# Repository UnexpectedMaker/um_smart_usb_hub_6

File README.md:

# Smart 6 Port USB Hub

**Automated testing. Automated device control.**

**Designed and made by [Unexpected Maker](https://unexpectedmaker.com) ·
[Get one from the store →](https://unexpectedmaker.com/shop/smarthub)**

Built for developers, test benches and USB devices that need to run unattended.
Smart USB Hub brings repeatable testing and everyday device routines to your
workbench, without the constant plugging, unplugging and reaching for cables.

## What it does

**Power cycling, scripted.** Use the REST API to switch a device's power, read
its voltage, current and power consumption, and check port status from your
test scripts. Repeat a startup test or compare readings across operating states
while the other devices stay powered.

**Every port, scheduled.** Set a different schedule for each port: selected
weekdays, a fixed run time, a chosen stop time or repeating intervals. Rules run
on the hub, so your browser doesn't need to stay open.

**Step in any time.** Open the web interface over Wi-Fi to switch an individual
port or investigate a device. Live readings show what it's drawing; connection
and fault status help you see why it isn't behaving as expected.

## Specifications

| | |
|---|---|
| Downstream | 6 × USB-C · USB 2.0 High Speed (480 Mbps) on every port |
| Upstream | 1 × USB-C · USB 2.0 High Speed (480 Mbps) |
| Hub chip | WCH CH339W · Multi-TT: every port has its own transaction translator, so full-speed and low-speed devices don't share bandwidth |
| Controller | ESP32-S3-WROOM-1 · 16 MB flash · 8 MB PSRAM |
| Port power | 5V USB-C input · 3A+ supply |
| 3V3 power | 2 × 3.3V LDOs · headroom for the ESP32-S3, hub chip, peripherals and LEDs |
| Protection | Per-port current limiting and over-current fault detection |
| Monitoring | Per-port voltage, current and power |
| Indicators | Per-port RGB status · power, device presence and faults |
| Environment | Onboard temperature and humidity sensor |
| Buttons | IO48 user button · IO0 / Boot · Reset |
| Case size | 90 mm × 64 mm × 19 mm |

## Web interface

## It's open source

Smart USB Hub is fully open source, so you can see exactly how it works, tweak
it to suit your bench, or build your own. Everything is in this repository:

| Folder | Contents |
|---|---|
| [`firmware/`](firmware/) | The PlatformIO project — building, flashing, first-time Wi-Fi setup and how to use the hub |
| [`hardware/`](hardware/) | KiCad 10 design files: schematic, PCB, footprints, 3D models and interactive BOM |
| [`docs/`](docs/) | Documentation: the [JSON / REST API reference](docs/rest_api.md), [port profiler](docs/profiler.md), [graph history](docs/graph_history.md) and [planned future updates](docs/future_updates.md) |
| [`step/`](step/) | STEP models of the board and the case, the light pipe insert, and the parts list for printing your own case |

Each folder has its own README with the details.

## Optional case

Add the case from the [store](https://unexpectedmaker.com/shop/smarthub) and
your hub goes from bare board to finished desk tool:

- **Matt black ABS** — a 3D printed enclosure that looks right at home on any
  bench
- **Laser cut light pipes** — every port's RGB status still shines through
- **Heat inserts + screws** — proper threads, so it goes together solid
- **Rubber feet** — it stays put when you plug and unplug

Or print your own from the files in [`step/`](step/) — its README covers the
light pipe insert and the screws, inserts and feet you'll need.

## Getting started

If you have a hub, start with **First-time setup** in the
[firmware README](firmware/README.md#first-time-setup). It gets the hub onto
your Wi-Fi so you can use the web interface.

## Licence

Copyright (c) 2026 [Unexpected Maker](https://unexpectedmaker.com).

| Part | Licence |
|---|---|
| Hardware (`hardware/`) and 3D files (`step/`) | [CERN-OHL-S v2](hardware/LICENSE) — strongly reciprocal: if you distribute the design, a modified version, or hardware made from it, you must publish the complete design source under the same licence |
| Firmware (`firmware/`) | [GPL-3.0-or-later](firmware/LICENSE) — use it, change it, put it in your own products; if you distribute it, you must publish the complete firmware source under the same licence. Bundled third-party code keeps its own licence (see the [firmware README](firmware/README.md#third-party-code)) |

Source location: <https://github.com/UnexpectedMaker/um_smart_usb_hub_6>

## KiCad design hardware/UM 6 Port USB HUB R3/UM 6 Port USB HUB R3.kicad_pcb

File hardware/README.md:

# Hardware

KiCad 10 project for the Unexpected Maker 6 Port Smart USB Hub (R3).

Open `UM 6 Port USB HUB R3/UM 6 Port USB HUB R3.kicad_pro` in KiCad 10 or later.

## Self-contained project

Everything that is not part of a standard KiCad installation is included in the project folder. No external or personal libraries are needed, and there are no absolute paths in any project file.

- **Footprints** – every non-stock footprint used on the board lives in the project library `UM_Hub.pretty`. It is registered through the project `fp-lib-table` using `${KIPRJMOD}`, so KiCad picks it up automatically when the project is opened.
- **3D models** – every non-stock model is in `3d models/` and is referenced relative to the project (`${KIPRJMOD}/3d models/...`). The 0805 resistor model is embedded in its footprint.
- **Stock parts** – the remaining footprints and models come from the default libraries installed with KiCad (`Capacitor_SMD`, `Package_DFN_QFN`, `Package_TO_SOT_SMD`, `RF_Module`, `MountingHole` and the standard `KICAD*_3DMODEL_DIR` models).
- **Symbols** – the schematic carries its own copy of every symbol it uses, so it opens and edits without any external symbol libraries.

## Contents of `UM 6 Port USB HUB R3/`

| Item | What it is |
|---|---|
| `UM 6 Port USB HUB R3.kicad_pro` | KiCad project file |
| `UM 6 Port USB HUB R3.kicad_sch` | Schematic |
| `UM 6 Port USB HUB R3.kicad_pcb` | PCB layout |
| `UM_Hub.pretty/` | Project footprint library (17 footprints) |
| `fp-lib-table` | Registers `UM_Hub` for this project |
| `3d models/` | STEP models for the non-stock parts |
| `bom/ibom.html` | Interactive HTML BOM |

## Manufacturing

If you are getting this board manufactured, the PCB stackup must match the following so that the USB differential pairs are impedance matched.

PCB Stackup: JLC04161H-3313 (Finished thickness 1.56mm ±10%)

90R Diff Pair Impedance:
- Trace 0.1545mm
- Gap 0.232mm
- Co-Planar Clearance 0.194mm

## Licence

Copyright (c) 2026 [Unexpected Maker](https://unexpectedmaker.com).

The hardware design files are licensed under the CERN Open Hardware Licence
Version 2 — Strongly Reciprocal (CERN-OHL-S v2). See [LICENSE](LICENSE).

If you distribute this design, a modified version of it, or hardware made from
it, you must make the complete design source available under the same licence.

Source location: <https://github.com/UnexpectedMaker/um_smart_usb_hub_6>

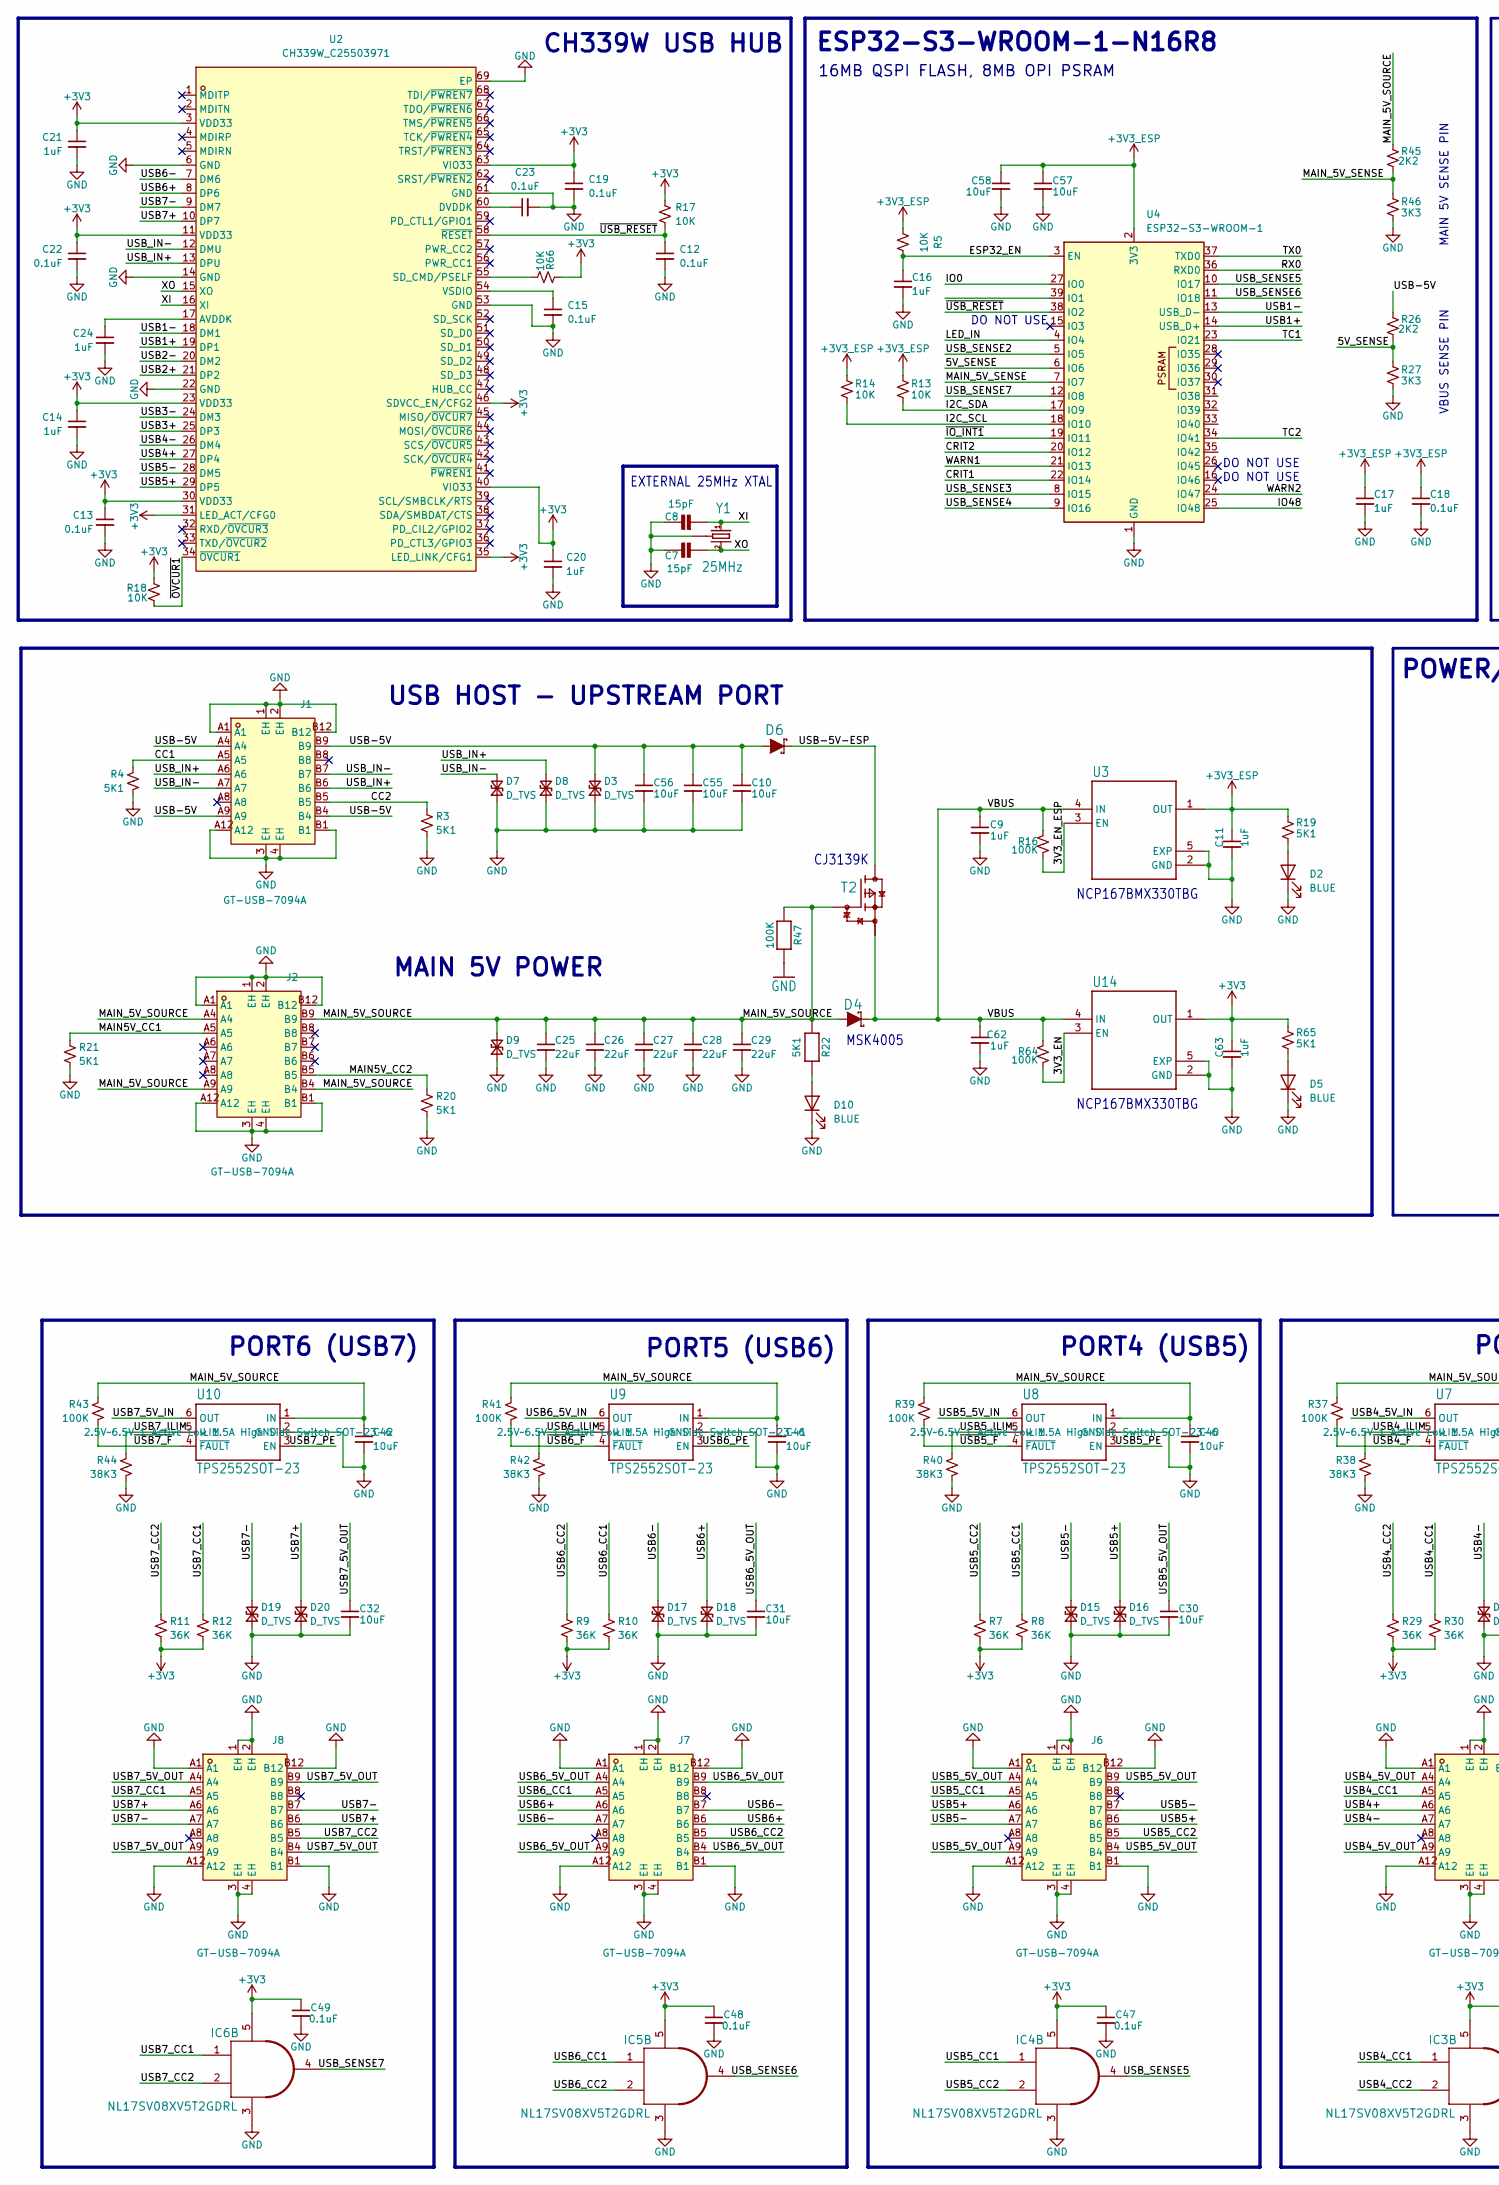
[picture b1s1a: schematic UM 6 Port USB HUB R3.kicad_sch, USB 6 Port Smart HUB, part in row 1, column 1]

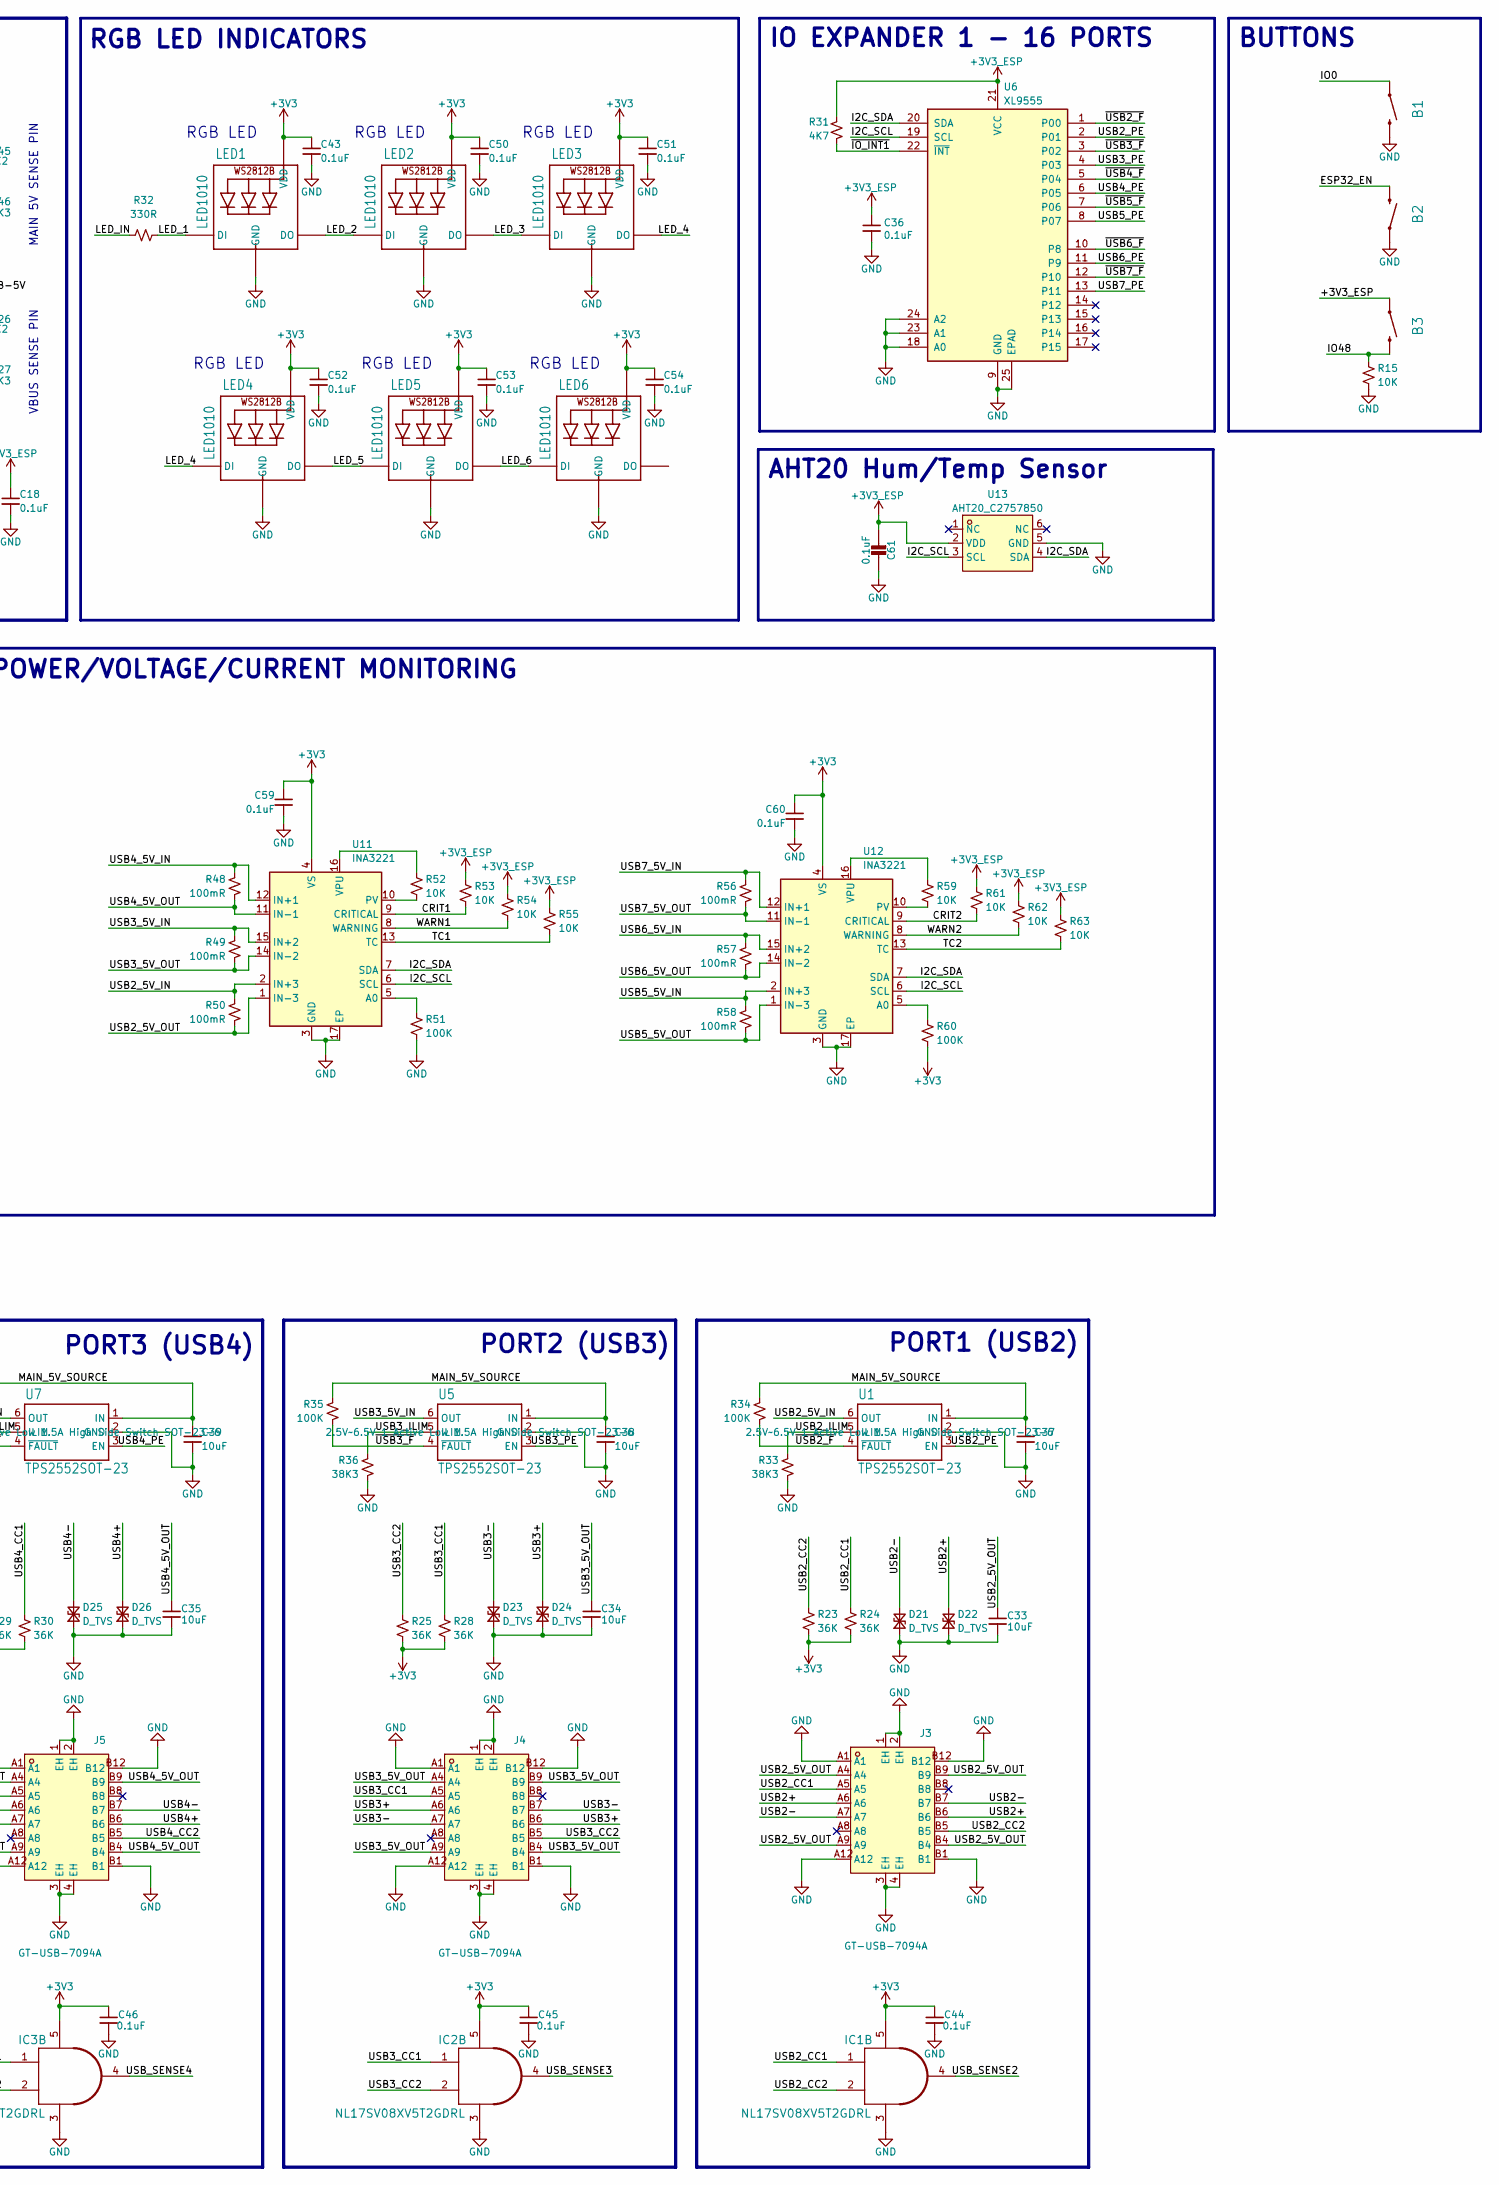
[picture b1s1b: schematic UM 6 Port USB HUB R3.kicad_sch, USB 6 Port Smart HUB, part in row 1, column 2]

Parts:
B1, B2, B3: MOMENTARY-SWITCH-SPST-PTH-RIGHT-ANGLE-KIT; SMT_SWITCH_TS-1091C-A6B3-D2; MPN TS-1091C-A7B3-D2
C7, C8: 15pF; C_0402_NEW; MPN CC0402FRNPO9BN150
C9, C11, C14, C16, C17, C20, C21, C24, C62, C63: 1uF; C_0402_NEW; MPN CL05A105KA5NQNC
C10, C30, C31, C32, C33, C34, C35, C37, C38, C39, C40, C41, C42, C55, C56, C57, C58: 10uF; C_0603_NEW; MPN CGA0603X5R106K250JT
C12, C13, C15, C18, C19, C22, C23, C36, C43, C44, C45, C46, C47, C48, C49, C50, C51, C52, C53, C54, C59, C60, C61: 0.1uF; C_0402_NEW; MPN 0402B104K500CT
C25, C26, C27, C28, C29: 22uF; C_1210_3225Metric; MPN CC1210KKX5R8BB226
D2, D5, D10: BLUE; LED_0402_NEW; MPN TJ-S1005SW4TGLC6B-A5
D3, D7, D8, D9, D15, D16, D17, D18, D19, D20, D21, D22, D23, D24, D25, D26: D_TVS; TVS X1-DFN1006-2-BEST; MPN ESD05V88D-LC
D4, D6: DIODE-SCHOTTKYWIDE; SOD-523-MSK4010; MPN MSK4010
IC1, IC2, IC3, IC4, IC5, IC6: NL17SV08XV5T2GDRL; SOT553; MPN NL17SV08XV5T2GDRL
J1, J2, J3, J4, J5, J6, J7, J8: GT-USB-7094A; CONN-SMD_GT-USB-7094A; MPN GT-USB-7094A; LCSC Part C22383838
LED1, LED2, LED3, LED4, LED5, LED6: LED1010; MPN XL-1010RGBC-2812B
R3, R4, R19, R20, R21, R22, R65: 5K1; R_0402_NEW; MPN 0402WGF5101TCE
R5, R13, R14, R15, R17, R18, R52, R53, R54, R55, R59, R61, R62, R63, R66: 10K; R_0402_NEW; MPN 0402WGF1002TCE
R7, R8, R9, R10, R11, R12, R23, R24, R25, R28, R29, R30: 36K; R_0402_NEW; MPN RC0402FR-0736KL
R16, R34, R35, R37, R39, R41, R43, R47, R51, R60, R64: 100K; R_0402_NEW; MPN RC0402FR-07100KL
R26, R45: 2K2; R_0402_NEW; MPN RC0402FR-072K2L
R27, R46: 3K3; R_0402_NEW; MPN 0402WGF3301TCE
R31: 4K7; R_0402_NEW; MPN RT0402DRD074K7L
R32: 330R; R_0402_NEW; MPN RC0402FR-07442KL
R33, R36, R38, R40, R42, R44: 38K3; R_0402_NEW; MPN TC0225B3832TCC
R48, R49, R50, R56, R57, R58: 100mR; R_0805_NEW; MPN FBF05FTPR100
T2: P-FET; SOT723; MPN CJ3139K
U1, U5, U7, U8, U9, U10: TPS2552SOT-23; SOT-23-6; MPN TPS2552DBVR
U2: CH339W_C25503971; QFN-68_L8.0-W8.0-P0.40-BL-EP5.5; MPN CH339W; LCSC Part C25503971
U3, U14: NCP167BMX330TBG; VREG_NCP167BMX330TBG; MPN NCP167BMX330TBG
U4: ESP32-S3-WROOM-1; MPN ESP32-S3-WROOM-1
U6: XL9555; VQFN-24-1EP_4x4mm_P0.5mm_EP2.45x2.45mm; MPN XL9555QF24
U11, U12: INA3221; Texas_RGV0016A_VQFN-16-1EP_4x4mm_P0.65mm_EP2.1x2.1mm; MPN INA3221AIRGVR
U13: AHT20_C2757850; SENSOR-SMD_L3.0-W3.0-P1.00-BR; MPN AHT20; LCSC Part C2757850
Y1: 25MHz; CRYSTAL_2.5X2; MPN 2TJ425000UYFBC

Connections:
+3V3: C13.1, C14.1, C19.1, C20.1, C21.1, C22.1, C43.1, C44.1, C45.1, C46.1, C47.1, C48.1, C49.1, C50.1, C51.1, C52.1, C53.1, C54.1, C59.1, C60.1, C63.1, IC1.5 (PWR), IC2.5 (PWR), IC3.5 (PWR), IC4.5 (PWR), IC5.5 (PWR), IC6.5 (PWR), LED1.VDD, LED2.VDD, LED3.VDD, LED4.VDD, LED5.VDD, LED6.VDD, R7.2, R8.2, R9.2, R10.2, R11.2, R12.2, R17.1, R18.1, R23.2, R24.2, R25.2, R28.2, R29.2, R30.2, R60.2, R65.1, R66.1, U2.3 (VDD33), U2.11 (VDD33), U2.23 (VDD33), U2.30 (VDD33), U2.31 (LED_ACT/CFG0), U2.35 (LED_LINK/CFG1), U2.40 (VIO33), U2.46 (SDVCC_EN/CFG2), U2.63 (VIO33), U11.4 (VS), U12.4 (VS), U14.1 (OUT)
+3V3_ESP: B3.1, C11.1, C17.1, C18.1, C36.1, C57.1, C58.1, C61.2, R5.1, R13.1, R14.1, R19.1, R31.1, R53.1, R54.1, R55.1, R61.1, R62.1, R63.1, U3.1 (OUT), U4.2 (3V3), U6.21 (VCC), U13.2 (VDD)
/3V3_EN: R64.2, U14.3 (EN)
/3V3_EN_ESP: R16.2, U3.3 (EN)
/5V_SENSE: R26.1, R27.2, U4.6 (IO6)
/CC1: J1.A5, R4.1
/CC2: J1.B5, R3.1
/CRIT1: R53.2, U4.22 (IO14), U11.9 (CRITICAL)
/CRIT2: R61.2, U4.20 (IO12), U12.9 (CRITICAL)
/ESP32_EN: B2.2, C16.1, R5.2, U4.3 (EN)
/I2C_SCL: R14.2, U4.18 (IO10), U6.19 (SCL), U11.6 (SCL), U12.6 (SCL), U13.3 (SCL)
/I2C_SDA: R13.2, U4.17 (IO9), U6.20 (SDA), U11.7 (SDA), U12.7 (SDA), U13.4 (SDA)
/IO0: B1.1, U4.27 (IO0)
/IO48: B3.2, R15.1, U4.25 (IO48)
/LED_1: LED1.DIN (DI), R32.1
/LED_2: LED1.DOUT (DO), LED2.DIN (DI)
/LED_3: LED2.DOUT (DO), LED3.DIN (DI)
/LED_4: LED3.DOUT (DO), LED4.DIN (DI)
/LED_5: LED4.DOUT (DO), LED5.DIN (DI)
/LED_6: LED5.DOUT (DO), LED6.DIN (DI)
/LED_IN: R32.2, U4.4 (IO4)
/MAIN5V_CC1: J2.A5, R21.1
/MAIN5V_CC2: J2.B5, R20.1
/MAIN_5V_SENSE: R45.1, R46.2, U4.7 (IO7)
/MAIN_5V_SOURCE: C25.1, C26.1, C27.1, C28.1, C29.1, C37.1, C38.1, C39.1, C40.1, C41.1, C42.1, D4.A, D9.2 (A2), J2.A4, J2.A9, J2.B4, J2.B9, R22.1, R34.1, R35.1, R37.1, R39.1, R41.1, R43.1, R45.2, R47.1, T2.1 (G), U1.1 (IN), U5.1 (IN), U7.1 (IN), U8.1 (IN), U9.1 (IN), U10.1 (IN)
/RX0: U4.36 (RXD0)
/TC1: R55.2, U4.23 (IO21), U11.13 (TC)
/TC2: R63.2, U4.34 (IO41), U12.13 (TC)
/TX0: U4.37 (TXD0)
/USB1+: U2.19 (DP1), U4.14 (USB_D+)
/USB1-: U2.18 (DM1), U4.13 (USB_D-)
/USB2+: D22.2 (A2), J3.A6, J3.B6, U2.21 (DP2)
/USB2-: D21.2 (A2), J3.A7, J3.B7, U2.20 (DM2)
/USB2_5V_IN: R50.1, U1.6 (OUT), U11.2 (IN+3)
/USB2_5V_OUT: C33.1, J3.A4, J3.A9, J3.B4, J3.B9, R50.2, U11.1 (IN-3)
/USB2_CC1: IC1.1 (PWR), J3.A5, R24.1
/USB2_CC2: IC1.2 (I1), J3.B5, R23.1
/USB2_ILIM: R33.1, U1.5 (ILIM)
/USB2_PE: U1.3 (EN), U6.2 (P01)
/USB3+: D24.2 (A2), J4.A6, J4.B6, U2.25 (DP3)
/USB3-: D23.2 (A2), J4.A7, J4.B7, U2.24 (DM3)
/USB3_5V_IN: R49.1, U5.6 (OUT), U11.15 (IN+2)
/USB3_5V_OUT: C34.1, J4.A4, J4.A9, J4.B4, J4.B9, R49.2, U11.14 (IN-2)
/USB3_CC1: IC2.1 (PWR), J4.A5, R28.1
/USB3_CC2: IC2.2 (I1), J4.B5, R25.1
/USB3_ILIM: R36.1, U5.5 (ILIM)
/USB3_PE: U5.3 (EN), U6.4 (P03)
/USB4+: D26.2 (A2), J5.A6, J5.B6, U2.27 (DP4)
/USB4-: D25.2 (A2), J5.A7, J5.B7, U2.26 (DM4)
/USB4_5V_IN: R48.1, U7.6 (OUT), U11.12 (IN+1)
/USB4_5V_OUT: C35.1, J5.A4, J5.A9, J5.B4, J5.B9, R48.2, U11.11 (IN-1)
/USB4_CC1: IC3.1 (PWR), J5.A5, R30.1
/USB4_CC2: IC3.2 (I1), J5.B5, R29.1
/USB4_ILIM: R38.1, U7.5 (ILIM)
/USB4_PE: U6.6 (P05), U7.3 (EN)
/USB5+: D16.2 (A2), J6.A6, J6.B6, U2.29 (DP5)
/USB5-: D15.2 (A2), J6.A7, J6.B7, U2.28 (DM5)
/USB5_5V_IN: R58.1, U8.6 (OUT), U12.2 (IN+3)
/USB5_5V_OUT: C30.1, J6.A4, J6.A9, J6.B4, J6.B9, R58.2, U12.1 (IN-3)
/USB5_CC1: IC4.1 (PWR), J6.A5, R8.1
/USB5_CC2: IC4.2 (I1), J6.B5, R7.1
/USB5_ILIM: R40.1, U8.5 (ILIM)
/USB5_PE: U6.8 (P07), U8.3 (EN)
/USB6+: D18.2 (A2), J7.A6, J7.B6, U2.8 (DP6)
/USB6-: D17.2 (A2), J7.A7, J7.B7, U2.7 (DM6)
/USB6_5V_IN: R57.1, U9.6 (OUT), U12.15 (IN+2)
/USB6_5V_OUT: C31.1, J7.A4, J7.A9, J7.B4, J7.B9, R57.2, U12.14 (IN-2)
/USB6_CC1: IC5.1 (PWR), J7.A5, R10.1
/USB6_CC2: IC5.2 (I1), J7.B5, R9.1
/USB6_ILIM: R42.1, U9.5 (ILIM)
/USB6_PE: U6.11 (P9), U9.3 (EN)
/USB7+: D20.2 (A2), J8.A6, J8.B6, U2.10 (DP7)
/USB7-: D19.2 (A2), J8.A7, J8.B7, U2.9 (DM7)
/USB7_5V_IN: R56.1, U10.6 (OUT), U12.12 (IN+1)
/USB7_5V_OUT: C32.1, J8.A4, J8.A9, J8.B4, J8.B9, R56.2, U12.11 (IN-1)
/USB7_CC1: IC6.1 (PWR), J8.A5, R12.1
/USB7_CC2: IC6.2 (I1), J8.B5, R11.1
/USB7_ILIM: R44.1, U10.5 (ILIM)
/USB7_PE: U6.13 (P11), U10.3 (EN)
/USB-5V: C10.1, C55.1, C56.1, D3.2 (A2), D6.A, J1.A4, J1.A9, J1.B4, J1.B9, R26.2
/USB-5V-ESP: D6.C, T2.3 (D)
/USB_IN+: D8.2 (A2), J1.A6, J1.B6, U2.13 (DPU)
/USB_IN-: D7.2 (A2), J1.A7, J1.B7, U2.12 (DMU)
/USB_SENSE2: IC1.4 (O), U4.5 (IO5)
/USB_SENSE3: IC2.4 (O), U4.8 (IO15)
/USB_SENSE4: IC3.4 (O), U4.9 (IO16)
/USB_SENSE5: IC4.4 (O), U4.10 (IO17)
/USB_SENSE6: IC5.4 (O), U4.11 (IO18)
/USB_SENSE7: IC6.4 (O), U4.12 (IO8)
/VBUS: C9.1, C62.1, D4.C, R16.1, R64.1, T2.2 (S), U3.4 (IN), U14.4 (IN)
/WARN1: R54.2, U4.21 (IO13), U11.8 (WARNING)
/WARN2: R62.2, U4.24 (IO47), U12.8 (WARNING)
/XI: C8.2, U2.16 (XI), Y1.1
/XO: C7.2, U2.15 (XO), Y1.3 (2)
/~IO_INT1: R31.2, U4.19 (IO11), U6.22 (~INT)
/~OVCUR1: R18.2, U2.34 (~OVCUR1)
/~USB2_F: R34.2, U1.4 (~FAULT), U6.1 (P00)
/~USB3_F: R35.2, U5.4 (~FAULT), U6.3 (P02)
/~USB4_F: R37.2, U6.5 (P04), U7.4 (~FAULT)
/~USB5_F: R39.2, U6.7 (P06), U8.4 (~FAULT)
/~USB6_F: R41.2, U6.10 (P8), U9.4 (~FAULT)
/~USB7_F: R43.2, U6.12 (P10), U10.4 (~FAULT)
/~USB_RESET: C12.1, R17.2, U2.58 (~RESET), U4.38 (IO2)
GND: B1.2, B2.1, C7.1, C8.1, C9.2, C10.2, C11.2, C12.2, C13.2, C14.2, C15.2, C16.2, C17.2, C18.2, C19.2, C20.2, C21.2, C22.2, C23.2, C24.2, C25.2, C26.2, C27.2, C28.2, C29.2, C30.2, C31.2, C32.2, C33.2, C34.2, C35.2, C36.2, C37.2, C38.2, C39.2, C40.2, C41.2, C42.2, C43.2, C44.2, C45.2, C46.2, C47.2, C48.2, C49.2, C50.2, C51.2, C52.2, C53.2, C54.2, C55.2, C56.2, C57.2, C58.2, C59.2, C60.2, C61.1, C62.2, C63.2, D2.1 (K), D3.1 (A1), D5.1 (K), D7.1 (A1), D8.1 (A1), D9.1 (A1), D10.1 (K), D15.1 (A1), D16.1 (A1), D17.1 (A1), D18.1 (A1), D19.1 (A1), D20.1 (A1), D21.1 (A1), D22.1 (A1), D23.1 (A1), D24.1 (A1), D25.1 (A1), D26.1 (A1), IC1.3 (GND), IC2.3 (GND), IC3.3 (GND), IC4.3 (GND), IC5.3 (GND), IC6.3 (GND), J1.1 (EH), J1.2 (EH), J1.3 (EH), J1.4 (EH), J1.A1, J1.A12, J1.B1, J1.B12, J2.1 (EH), J2.2 (EH), J2.3 (EH), J2.4 (EH), J2.A1, J2.A12, J2.B1, J2.B12, J3.1 (EH), J3.2 (EH), J3.3 (EH), J3.4 (EH), J3.A1, J3.A12, J3.B1, J3.B12, J4.1 (EH), J4.2 (EH), J4.3 (EH), J4.4 (EH), J4.A1, J4.A12, J4.B1, J4.B12, J5.1 (EH), J5.2 (EH), J5.3 (EH), J5.4 (EH), J5.A1, J5.A12, J5.B1, J5.B12, J6.1 (EH), J6.2 (EH), J6.3 (EH), J6.4 (EH), J6.A1, J6.A12, J6.B1, J6.B12, J7.1 (EH), J7.2 (EH), J7.3 (EH), J7.4 (EH), J7.A1, J7.A12, J7.B1, J7.B12, J8.1 (EH), J8.2 (EH), J8.3 (EH), J8.4 (EH), J8.A1, J8.A12, J8.B1, J8.B12, LED1.GND, LED2.GND, LED3.GND, LED4.GND, LED5.GND, LED6.GND, R3.2, R4.2, R15.2, R20.2, R21.2, R27.1, R33.2, R36.2, R38.2, R40.2, R42.2, R44.2, R46.1, R47.2, R51.2, U1.2 (GND), U2.6 (GND), U2.14 (GND), U2.22 (GND), U2.53 (GND), U2.61 (GND), U2.69 (EP), U3.2 (GND), U3.5 (EXP), U4.1 (GND), U4.40 (GND), U4.41 (GND), U5.2 (GND), U6.9 (GND), U6.18 (A0), U6.23 (A1), U6.24 (A2), U6.25 (EPAD), U7.2 (GND), U8.2 (GND), U9.2 (GND), U10.2 (GND), U11.3 (GND), U11.17 (EP), U12.3 (GND), U12.17 (EP), U13.5 (GND), U14.2 (GND), U14.5 (EXP), Y1.2 (GND), Y1.4 (GND)
unnamed: D2.2 (A), R19.2
unnamed: D5.2 (A), R65.2
unnamed: D10.2 (A), R22.2
unnamed: C24.1, U2.17 (AVDDK)
unnamed: C23.1, U2.60 (DVDDK)
unnamed: R66.2, U2.55 (SD_CMD/PSELF)
unnamed: C15.1, U2.54 (VSDIO)
unnamed: R51.1, U11.5 (A0)
unnamed: R52.2, U11.10 (PV)
unnamed: R52.1, U11.16 (VPU)
unnamed: R60.1, U12.5 (A0)
unnamed: R59.2, U12.10 (PV)
unnamed: R59.1, U12.16 (VPU)

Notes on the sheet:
PORT4 (USB5)
DO NOT USE
RGB LED
AHT20 Hum/Temp Sensor
PORT1 (USB2)
MAIN 5V POWER
ESP32-S3-WROOM-1-N16R8
16MB QSPI FLASH, 8MB OPI PSRAM
RGB LED INDICATORS
PORT6 (USB7)
USB HOST - UPSTREAM PORT
PORT3 (USB4)
CH339W USB HUB
VBUS SENSE PIN
PORT5 (USB6)
BUTTONS
NCP167BMX330TBG
POWER/VOLTAGE/CURRENT MONITORING
CJ3139K
MSK4005
MAIN 5V SENSE PIN
EXTERNAL 25MHz XTAL
IO EXPANDER 1 - 16 PORTS
PORT2 (USB3)

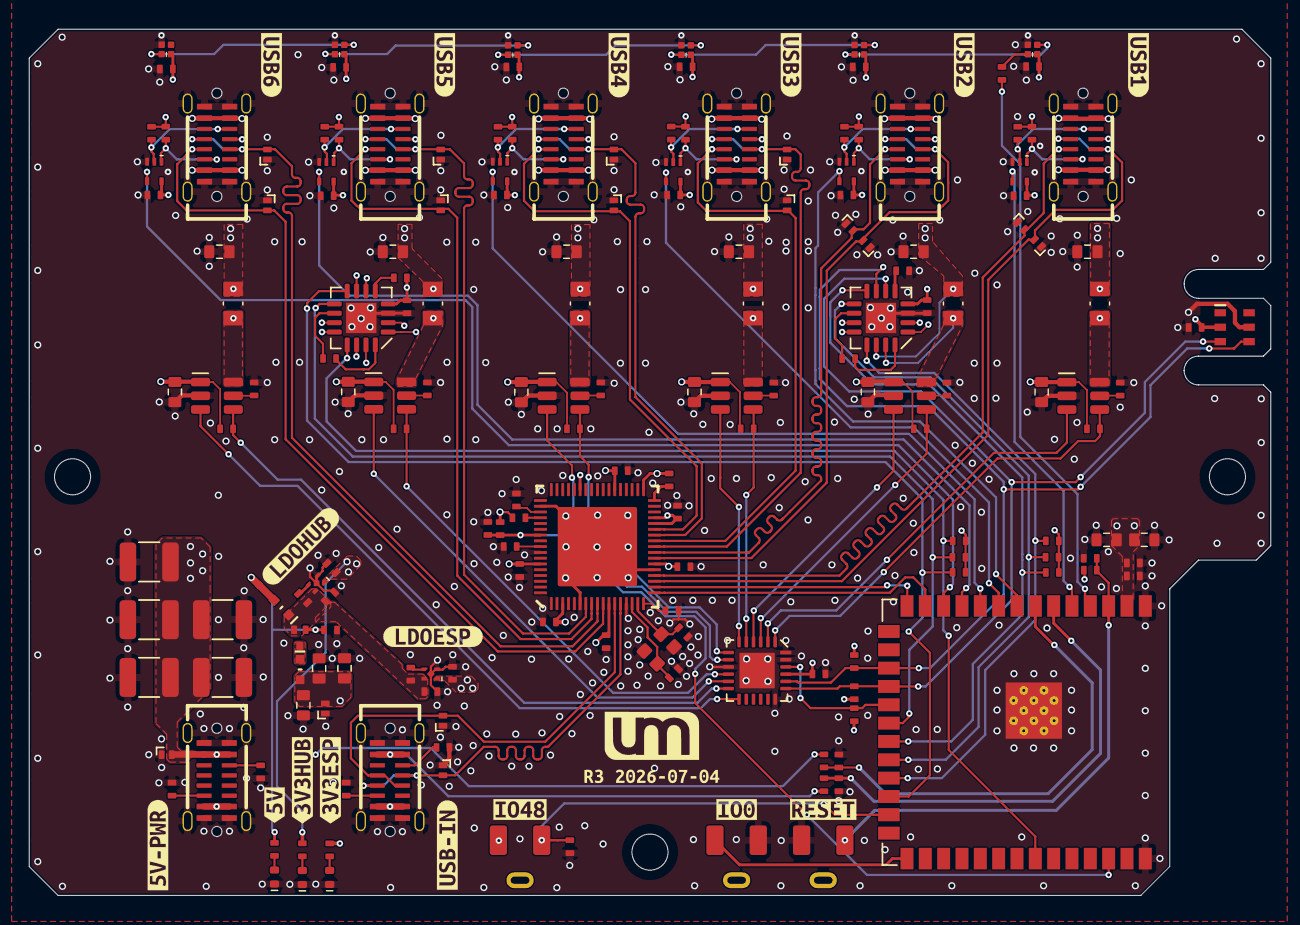
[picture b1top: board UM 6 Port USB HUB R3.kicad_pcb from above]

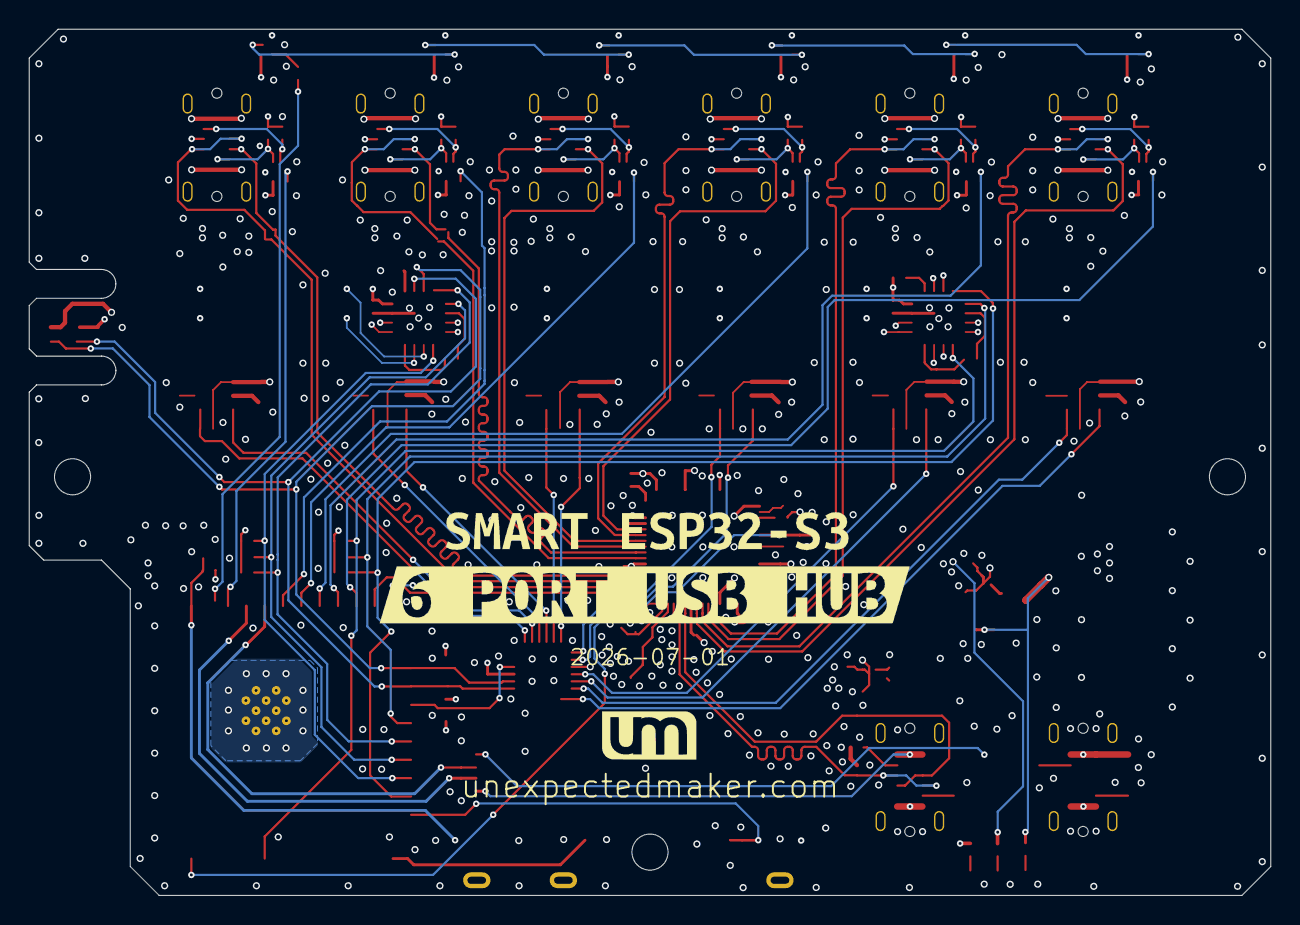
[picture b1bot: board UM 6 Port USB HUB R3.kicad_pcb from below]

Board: 4 copper layers, 86.0 x 60.0 mm, 200 parts (3 on the bottom side), 115 nets.

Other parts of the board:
U$2: UM_LOGONEW_SMALL; UM_LOGO_NEW_SMALL
kibuzzard-6A0CC55D: G***; kibuzzard-6A0CC55D
kibuzzard-6A0CC533: G***; kibuzzard-6A0CC533
kibuzzard-6A160FA6: G***; kibuzzard-6A160FA6
kibuzzard-6A160FAE: G***; kibuzzard-6A160FAE
kibuzzard-6A160FB8: G***; kibuzzard-6A160FB8
kibuzzard-6A160FBE: G***; kibuzzard-6A160FBE
kibuzzard-6A160FC5: G***; kibuzzard-6A160FC5
kibuzzard-6A447CB2: G***; kibuzzard-6A447CB2
kibuzzard-6A472ABE: G***; kibuzzard-6A472ABE
kibuzzard-6A1603D6: G***; kibuzzard-6A1603D6
kibuzzard-6A4480B2: G***; kibuzzard-6A4480B2
kibuzzard-6A4480C0: G***; kibuzzard-6A4480C0
kibuzzard-6A48901C: G***; kibuzzard-6A48901C
kibuzzard-6A48903D: G***; kibuzzard-6A48903D
kibuzzard-6A48904C: G***; kibuzzard-6A48904C
kibuzzard-6A48947B: G***; kibuzzard-6A48947B
kibuzzard-6A160306: G***; kibuzzard-6A160306
kibuzzard-6A160323: G***; kibuzzard-6A160323
kibuzzard-6A489058: G***; kibuzzard-6A489058

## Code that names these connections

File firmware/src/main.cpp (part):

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// ===========================================================================

// Shared I2C bus: I/O expander (0x20), INA3221 x2 (0x40, 0x41), AHT20 (0x38).
#define I2C_SDA 9
#define I2C_SCL 10
#define EXP_INT_PIN 11 // I/O expander INT, active LOW, open-drain
#define BUTTON_PIN 48  // user button, external pull-down, pressed = HIGH
#define LED_PIN 4      // WS2812B data, one LED per port
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#define INA2_WARN_PIN 47

// Hub IC reset, active LOW. Wired, but not used by the firmware.
#define USB_RESET_PIN 2

// 5V present-sense lines. HIGH = present.
#define MAIN_5V_SENSE_PIN 7     // the separate 5V input that powers the ports
#define UPSTREAM_5V_SENSE_PIN 6 // the upstream (host) USB connector

// ===========================================================================
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        port.applyFault(reg0, reg1);
}

bool main5vPresent() { return digitalRead(MAIN_5V_SENSE_PIN) == HIGH; }
bool upstream5vPresent() { return digitalRead(UPSTREAM_5V_SENSE_PIN) == HIGH; }

// One port's measurements. ok = false when that port's INA3221 isn't fitted, or
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    pinMode(EXP_INT_PIN, INPUT_PULLUP);
    attachInterrupt(digitalPinToInterrupt(EXP_INT_PIN), onExpanderInt, FALLING);
    pinMode(BUTTON_PIN, INPUT);
    pinMode(MAIN_5V_SENSE_PIN, INPUT);
    pinMode(UPSTREAM_5V_SENSE_PIN, INPUT);
    for (uint8_t p : {INA1_TC_PIN, INA1_CRIT_PIN, INA1_WARN_PIN, INA2_TC_PIN, INA2_CRIT_PIN, INA2_WARN_PIN})
        pinMode(p, INPUT);
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

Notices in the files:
firmware/src/main.cpp:
SPDX-License-Identifier: GPL-3.0-or-later
License, version 3 or (at your option) any later version. See LICENSE.
